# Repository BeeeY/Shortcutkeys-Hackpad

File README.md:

# Shortcutkeys

A simple direct pin macropad for a 6 shortcuts : copy, paste, new tab, close tab, undo, redo.

## BOM
1 unsoldered Seeed XIAO RP2040

6x MX-Style switches

6x white blank DSA keycaps

4x M3x16mm screws

4x M3x5mx4mm heatset inserts

## Schematic & PCB

## Case

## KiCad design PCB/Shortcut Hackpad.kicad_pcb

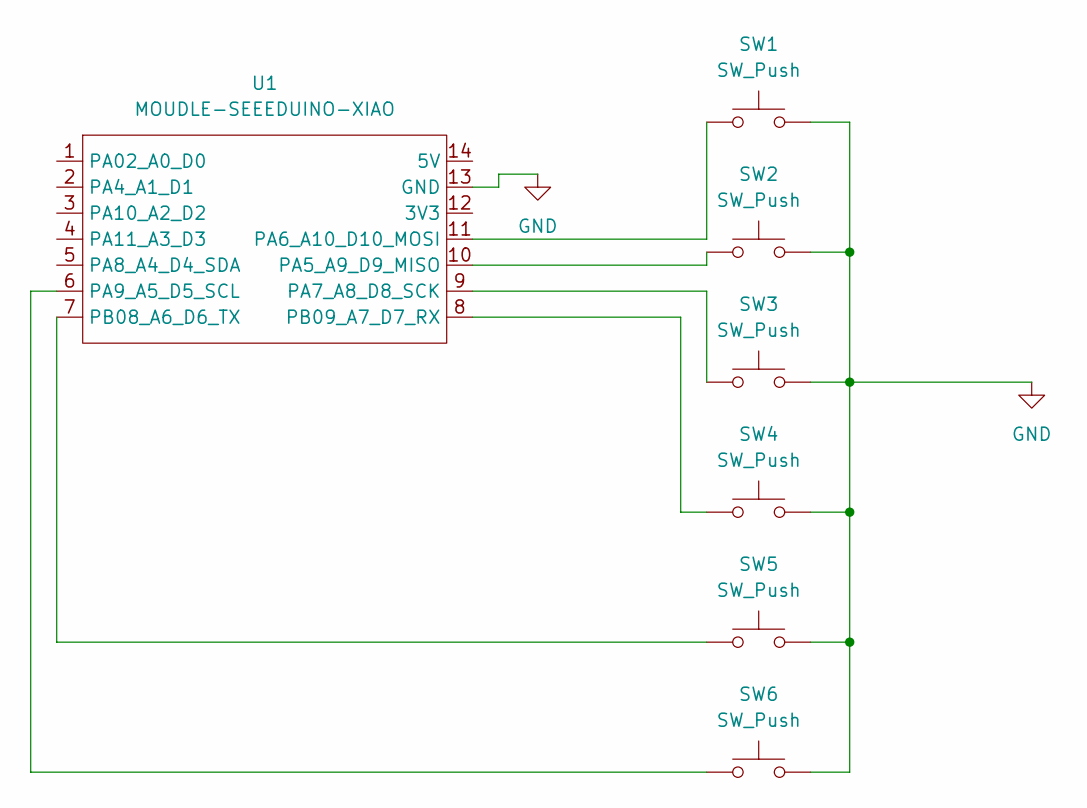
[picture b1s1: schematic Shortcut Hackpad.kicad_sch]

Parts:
SW1, SW2, SW3, SW4, SW5, SW6: SW_Push; SW_Cherry_MX_1.00u_PCB
U1: MOUDLE-SEEEDUINO-XIAO; XIAO-Generic-Hybrid-14P-2.54-21X17.8MM

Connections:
GND: SW1.2, SW2.2, SW3.2, SW4.2, SW5.2, SW6.2, U1.13 (GND)
unnamed: SW2.1, U1.10 (PA5_A9_D9_MISO)
unnamed: SW1.1, U1.11 (PA6_A10_D10_MOSI)
unnamed: SW3.1, U1.9 (PA7_A8_D8_SCK)
unnamed: SW6.1, U1.6 (PA9_A5_D5_SCL)
unnamed: SW5.1, U1.7 (PB08_A6_D6_TX)
unnamed: SW4.1, U1.8 (PB09_A7_D7_RX)

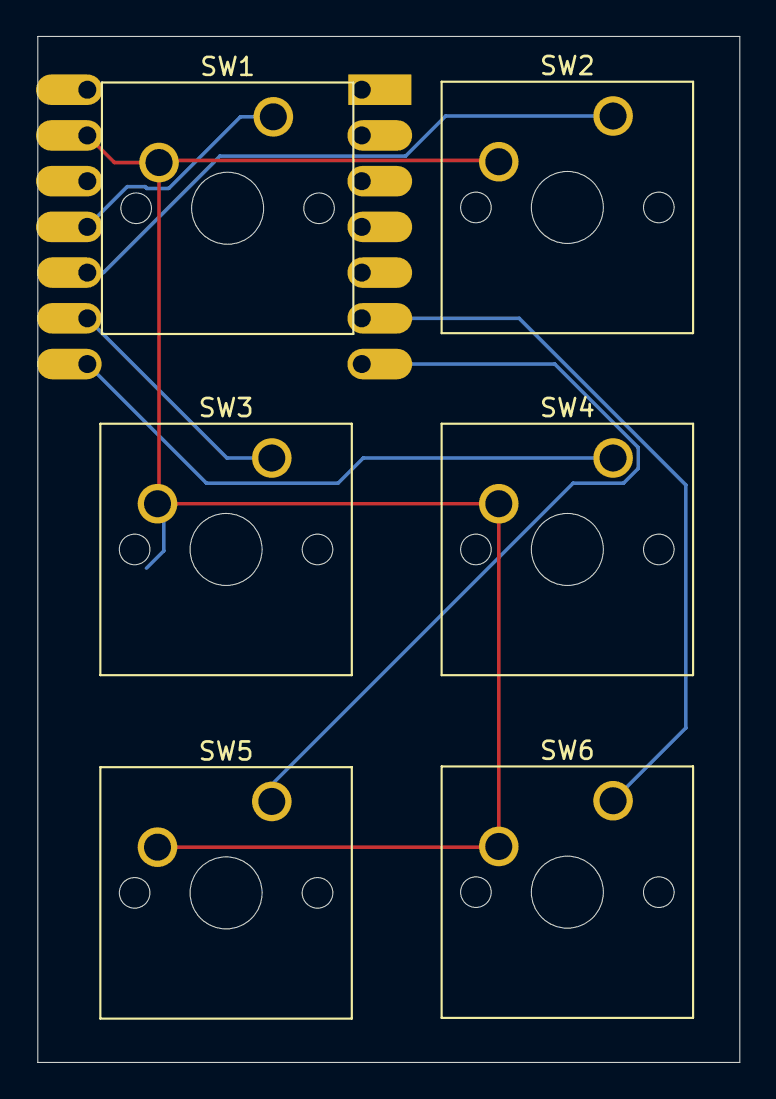
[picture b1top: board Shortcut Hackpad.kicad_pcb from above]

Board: 2 copper layers, 39.0 x 57.0 mm, 7 parts (1 on the bottom side), 7 nets.
